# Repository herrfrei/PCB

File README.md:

Dieses Werk ist lizenziert unter einer [Creative Commons Namensnennung - Nicht-kommerziell - Weitergabe unter gleichen Bedingungen 4.0 International Lizenz](http://creativecommons.org/licenses/by-nc-sa/4.0/).

Bei Nutzung der Platinen freue ich mich über Feedback und kleine Aufmerksamkeiten aus meiner [Amazon Wunschliste](https://www.amazon.de/gp/registry/wishlist/3NNUQIQO20AAP/ref=nav_wishlist_lists_1).

# PCB
## HB-RF-USB
Eine Platine um die Homematic Funkmodule HM-MOD-RPI-PCB und RF-RPI-MOD per USB anschließen zu können.

[Schaltplan](HB-RF-USB/HB-RF-USB.pdf)

### Benötigte Bauteile:
* 1x FTDI FT232RL (U1)
* 1x Micro USB Connector MK5P
* 1x Kerko 4.7nF 0805 (C9)
* 1x Kerko 10nF 0805 (C7)
* 6x Kerko 100nF 0805 (C1-C6)
* 1x Kerko 4.7uF 0805 (C8)
* 2x Widerstand 1K 0805 (R2, R3)
* 2x Widerstand 10K 0805 (R1, R5)
* 1x Widerstand 1M 0805 (R4)
* 1x Ferritperle 30 Ohm 0805 (L1)
* 2x IRLML6402 (Q1, Q2)
* 1x IRLML2502 (Q1)
* 1x Pinheader 2*6
* 1x Pinheader 2*20

### EEPROM flashen
Das EEPROM des FT232RL muss mit dem Programm [FT_Prog](https://www.ftdichip.com/Support/Utilities.htm#FT_PROG) programmiert werden. Ein passendes Template findet sich [hier](HB-RF-USB/FT232R_Template.xml).
Die Platine benötigt spezielle Treiber, diese sind in [piVCCU3](https://github.com/alexreinert/piVCCU) ab Version 3.41.11-13 eingebaut.

## HB-UNI-SEN-BATT
Eine universelle Platine für Homebrew Geräte basierend auf [AskSin++ Library](https://github.com/pa-pa/AskSinPP)

[Schaltplan](HB-UNI-SEN-BATT/HB-UNI-SEN-BATT.pdf)

### Benötigte Bauteile:
* Arduino Pro Mini 3.3V 8Mhz (The Simple)
* CC1101 Modulplatine 868MHz
* 2x LEDs 3mm Low Current (Pin 4 und 5)
* 2x 470Ohm Widerstände (Vorwiderstand für LEDs)
* Elko 10uF 1,5mm
* 2x Goobay Batteriehalter Mignon Print
* Mikroschalter 6*6mm
* Stiftleiste RM 2mm 1x8 Pin (Für CC1101)
* Stiftleiste RM 2,54MM (nach Bedarf)
* IRLU024N (optional für Verpolungsschutz)
* 100KOhm Widerstand (optional für Verpolungsschutz)
* 2x 10KOhm Widerstand (optional Pullup für I2C)

### Passendes Gehäuse
* Camdenboss CBRS01SWH und CBRS01VWH

### Hinweise
* Achtung: Kein Überspannungschutz vorhanden
* Der Verpolungsschutz ist optional. Dafür Bauteil Q1 (IRLU024N) und R3 (100KOhm Widerstand) bestücken. Alternativ J8 auf der Platinenrückseite brücken um ohne Verpolungsschutz zu arbeiten.

## HB-UNI-SEN-PCB
Eine universelle Platine für Homebrew Geräte basierend auf [AskSin++ Library](https://github.com/pa-pa/AskSinPP)

[Schaltplan](HB-UNI-SEN-PCB/HB-UNI-SEN-PCB.pdf)

### Benötigte Bauteile:
* Arduino Pro Mini 3.3V 8Mhz (The Simple)
* CC1101 Modulplatine 868MHz
* 1x LEDs 3mm Low Current (Pin 4)
* 1x 470Ohm Widerstände (Vorwiderstand für LEDs)
* Mikroschalter 6*6mm
* Stiftleiste RM 2mm 1x8 Pin (Für CC1101)
* Stiftleiste RM 2,54MM (nach Bedarf)
* Optional: 2x 10KOhm Widerstand und 2x 10KOhm PTC (Temperaturmessung mit PTC an A0 und A1)

### Hinweise
* Achtung: kein Verpolungs- oder Überspannungschutz vorhanden
* Am I2C sind keine Pullups vorhanden, da diese im Regelfall auf I2C Platinen bereits integriert sind
* Aktuell fehlt noch ein Kondensator am VCC vom CC1101.

## HB-UNI-644 (Rev. 2)
Eine universelle Platine für Homebrew Geräte basierend auf [AskSin++ Library](https://github.com/pa-pa/AskSinPP) und dem ATmega644PA

[Schaltplan](HB-UNI-644/HB-UNI-644.pdf)

### Benötigte Bauteile:
#### Grundfunktion
* ATmega644PA oder ATmega1284P (TQFP44) (U1)
* CC1101 Modulplatine 868MHz ggf. mit RM 2.0 Pinheader (U2)
* 1x Kerko 10uF 0805 (C13)
* 7x Kerko 10nF 0805 (C1-C6, C14)
* 2x Widerstand 330 Ohm 0805 (R2, R3)
* 1x Widerstand 10K Ohm 0805 (R1)
* 1x Triple Color LED Common Cathode THT (D1)
* 1x Tactile Switch 2 Pin 6x3.5 SMD (SW1)
* 1x Quarz 8 Mhz HC49 THT (Y1) (optional)
* 2x Kerko 22pF 0805 (C7, C8) (optional für Quarz)
* Pinheader nach Bedarf

#### Power Option 1: Batteriebetrieb mit Step-Up
* 2x Goobay Batteriehalter Mignon Print
* 1x Widerstand 470K Ohm 0805 (R5)
* 1x Widerstand 100K Ohm 0805 (R6)
* 1x MAX1724EZK33 (U3)
* 1x LQH43CN100K03L (L1)
* 1x Kerko 10uF 0805 (C9)
* 1x Kerko 33uF 1206 (C10)
##### Verpolungsschutz und Überlastschutz
* 1x IRLML6244 (Q1)
* 1x Widerstand 100K Ohm 0805 (R4)
* 1x PTC 6V/250mA 1206 (F1)

#### Power Option 2: Externe Stromversorgung mit 5-9V, 100mA
* 1x HT-7533-1 (U4)
* 1x Kerko 10uF 50V 1206 (C11)
* 1x Kerko 10uF 0805 (C12)
* 1x Elko 1000uF 8mm*12mm (C15)
##### Verpolungsschutz und Überlastschutz
* 1x IRLML5203 (Q2)
* 1x Widerstand 100K Ohm 0805 (R11)
* 1x PTC 16V/250mA 1206 (F1)

#### Power Option 3: Externe Stromversorgung 5-24V, 1A
* 1x [MP2315 Power Module](https://de.aliexpress.com/item/DC-DC-R-cktritt-Abw-rtswandler-Einstellbar-4-5-V-24-V-zu-5-V-3A/32833398745.html)
   Kontakt zum Trimmer durchtrennen, Lötbrücke bei 3.3V anbringen
* 1x Elko 1000uF 8mm*12mm (C15)
##### Verpolungsschutz und Überlastschutz
* 1x IRF4905S (Q3)
* 1x Widerstand 100K Ohm 0805 (R12)
* 1x Zener 16V MiniMelf (D2)
* 1x PTC 30V/2A 1206 (F1)

#### I2C Pullup Widerstände (optional)
* 2x Widerstand 10k Ohm 0805 (R7, R8)

#### Vorwiderstände für NTC Messung an A0 und A1
* 2x Widerstand 10k Ohm 0805 (R9, R10)

### Passendes Gehäuse
* Camdenboss CBRS01SWH und CBRS01VWH

### Betrieb mit 5V, 16MHz bei Netzbetrieb
* Der MC kann auch mit 5V und dann mit 16MHz betrieben werden, dafür müssen ggü. oben folgende Anpassungen gemacht werden:
* Nicht möglich bei Power Option 1
* Bei Power Option 2: HT-7550-1 statt HT-7533-1 uf U4, Eingangsspannung >= 6V
* Bei Power Option 3: Lötbrücke auf MP2315 Modul bei 5V statt bei 3.3V, Eingangsspannung >= 6V
* CC1101 auf Position U5 statt auf U2
* Nicht bestücken: C13, C14
* Quarz Y1 mit 16MHz statt 8MHz
* Zusätzliche Bauteile
   * 1x LM-3480-3.3 (U6)
   * 1x TXS0108EPWR (U7)
   * 3x Kerko 10uF 0805 (C16, C18, C19)
   * 3x Kerko 10nF 0805 (C17, C20, C21)
* ACHTUNG: Alle VCC Pins laufen dann auf 5V, auch z.B. die vom I2C

### Hinweise
* Auch wenn die meisten Bauteile SMD sind, so ist die Platine für Handlötung entwickelt. Dementsprechend sind alle Teile mind. 0805 mit vergrößerten Pads für Handlötung.
* Es darf immer nur eine Power Option genutzt und bestückt werden
* Die rechte Seite der Platine kann entfernt werden, wenn die Batteriehalter oder das MP2315 Power Module nicht benötigt werden, es laufen keine Leiterbahnen rechts der Fräsung (abgesehen von denen für die Batterie bzw. Power Module)
* Die Lötbrücke J2 muss immer geschlossen werden, außer es wird der Verpolungsschutz für Batteriebetrieb verwendet
* Falls eine externe Spannung von 3.3V ohne Spannungsanpassung, Verpolungsschutz und Überlastschutz verwendet werden soll, dann muss die Lötbrücke J4 geschlossen werden
* Die Anschlüsse an J9 sind zusammen mit J12 genau passend für die Platine CJMCU-2803 um an den Anschlüssen ein Darlington Array zu verwenden (Jeder der Ports ist dann mit 500mA belastbar)
* Beschriftung der Anschlüsse folgt dem Bobuino Pinout

## HB-UNI-SEN-WEA
Eine passende Platine für den [Wettersensor von Jérôme](https://github.com/jp112sdl/HB-UNI-Sen-WEA/)

[Schaltplan](HB-UNI-SEN-WEA/HB-UNI-SEN-WEA.pdf)

### Benötigte Bauteile:
* Arduino Pro Mini 3.3V 8Mhz (The Simple)
* CC1101 Modulplatine 868MHz
* Elko 10uF 1,5mm
* Mikroschalter 6*6mm
* Kerko 1nf RM 2.5mm
* 10K Widerstand
* 100K Widerstand
* MPSA13 TO-92
* 4x Molex Spox 2-pol (Alternativ Stiftleiste oder Kabel direkt anlöten)
* 4x Molex Spox 4-pol (Alternativ Stiftleiste oder Kabel direkt anlöten)
* 1x Molex Spox 7-pol (Alternativ Stiftleiste oder Kabel direkt anlöten)
* Stiftleiste RM 2mm 1x8 Pin (Für CC1101)

### Hinweise
* Achtung: kein Verpolungs- oder Überspannungschutz vorhanden
* Am I2C sind keine Pullups vorhanden, da diese im Regelfall auf I2C Platinen bereits integriert sind

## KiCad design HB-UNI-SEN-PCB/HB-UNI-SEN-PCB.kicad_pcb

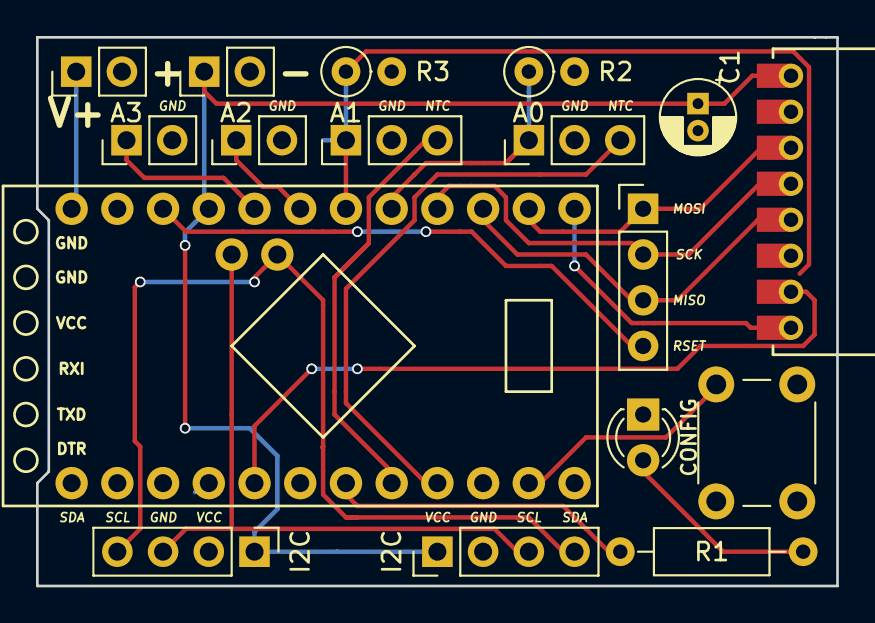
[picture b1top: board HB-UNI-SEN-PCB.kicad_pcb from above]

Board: 2 copper layers, 44.4 x 30.5 mm, 17 parts (0 on the bottom side), 20 nets.

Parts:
C1: 10uF; CP_Radial_D4.0mm_P1.50mm
D1: LED; LED_D3.0mm
J0: BATT; Pin_Header_Straight_1x02_Pitch2.54mm
J1: I2C_1; Pin_Header_Straight_1x04_Pitch2.54mm
J2: I2C_2; Pin_Header_Straight_1x04_Pitch2.54mm
J3: A0; Pin_Header_Straight_1x03_Pitch2.54mm
J4: A1; Pin_Header_Straight_1x03_Pitch2.54mm
J5: A2; Pin_Header_Straight_1x02_Pitch2.54mm
J6: A3; Pin_Header_Straight_1x02_Pitch2.54mm
J7: PROG; Pin_Header_Straight_1x04_Pitch2.54mm
JR1: RAW; PinHeader_1x02_P2.54mm_Vertical
R1: 470; R_Axial_DIN0207_L6.3mm_D2.5mm_P10.16mm_Horizontal
R2, R3: 10K; R_Axial_DIN0207_L6.3mm_D2.5mm_P2.54mm_Vertical
SW1: CONFIG_BUTTON; SW_PUSH_6mm_h5mm
U1: ArduinoProMini
U2: CC1101

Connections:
+3V3: C1.1, J0.1, J1.1, J2.1, U1.9, U2.1
+12V: JR1.1, U1.12
/A0: J3.1, R2.1, U1.5
/A1: J4.1, R3.1, U1.6
/A2: J5.1, U1.7
/A3: J6.1, U1.8
/D2: U1.17, U2.7
/D5: J4.3, U1.20
/D6: J3.3, U1.21
/MISO: J7.3, U1.3, U2.5
/MOSI: J7.1, U1.2, U2.3
/RSET: J7.4, U1.10
/SCK: J7.2, U1.4, U2.4
/SCL: J1.3, J2.3, U1.26
/SDA: J1.4, J2.4, U1.25
/SS: U1.1, U2.8
GND: C1.2, D1.1, J0.2, J1.2, J2.2, J3.2, J4.2, J5.2, J6.2, JR1.2, R2.2, R3.2, SW1.2, U1.11, U1.16, U2.2
unnamed: D1.2, R1.1
unnamed: R1.2, U1.19
unnamed: SW1.1, U1.23

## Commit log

2018-12-20 Added HB-RF-USB
2019-01-14 Fixed Readme
2019-02-21 Updated to v1.5: - Added raw power input - Moved two resistors and some jumpers - Rerouted some tracks
2019-02-21 Added missing capacitor at CC1101

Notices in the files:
README.md:
Creative Commons Lizenzvertrag
